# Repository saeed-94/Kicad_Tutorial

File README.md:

# Kicad Tutorial
* STM32F030 Circuit

*pcb Layout Top*

*pcb Layout Bottom*

## Shematic

## FreeCad
*pcb Layout Top*

*pcb Layout Top*

Hints:
* Circuit design in two layers with kicad version 5.1.5.

* 3D mode USB connector of the site: https://www.snapeda.com/parts/1050170001/Molex/view-part/?ref=search&t=USB_Micro-B_Molex-105017-0001

* In addition to wiring all routes, polygon is also considered ground and is located in the first layer.

* Circuit design with easyeda software: (Folder (doc)>-easyeda.pdf)

# Relay Module

*pcb Layout*

## Shematic

## FreeCad
*pcb 3d Layout*

For 3d Model we used kicadStepUpMod in FreeCAD software.

Hints:
* Circuit design in two layers with kicad version 5.1.9.

## Installing
Download and install your corresponding version of FreeCAD from https://wiki.freecadweb.org/Download

automatically using the FreeCAD Add-on Manager (https://github.com/FreeCAD/FreeCAD-addons) (bundled in to 0.17 dev version under Tools Menu)
manually by copying the kicadStepUpMod folder to the Mod sub-directory of the FreeCAD application.

## Designer
Saeed Ghorbani

Email: sa_ghorbani95@yahoo.com

Linkedin: www.linkedin.com/in/saeedghorbani

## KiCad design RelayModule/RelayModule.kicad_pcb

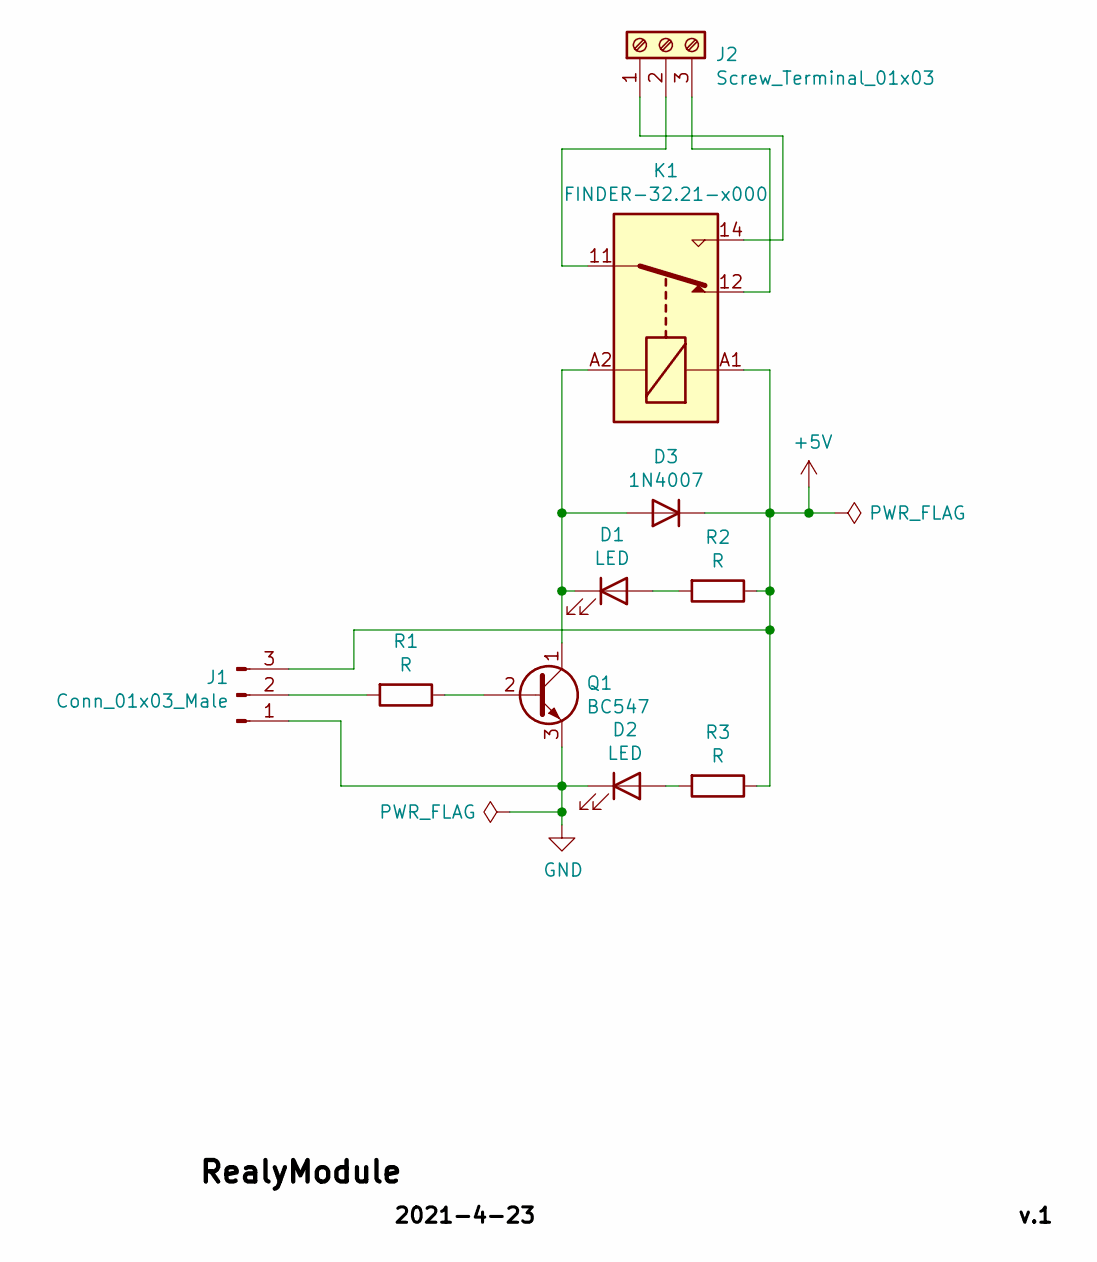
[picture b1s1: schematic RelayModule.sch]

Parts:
D1, D2: LED; LED_D3.0mm
D3: 1N4007; D_DO-41_SOD81_P10.16mm_Horizontal
J1: Conn_01x03_Male; PinHeader_1x03_P2.00mm_Vertical
J2: Screw_Terminal_01x03; TerminalBlock_Phoenix_MKDS-1,5-3_1x03_P5.00mm_Horizontal
K1: FINDER-32.21-x000; Relay_SPDT_Finder_36.11
Q1: BC547; TO-92
R1, R2, R3: R; R_Axial_DIN0411_L9.9mm_D3.6mm_P25.40mm_Horizontal

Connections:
+5V: D3.1 (K), J1.3, K1.A1, R2.1, R3.1
GND: D2.1 (K), J1.1, Q1.3 (E)
unnamed: D1.1 (K), D3.2 (A), K1.A2, Q1.1 (C)
unnamed: D1.2 (A), R2.2
unnamed: D2.2 (A), R3.2
unnamed: J1.2, R1.2
unnamed: J2.1, K1.14
unnamed: J2.2, K1.11
unnamed: J2.3, K1.12
unnamed: Q1.2 (B), R1.1

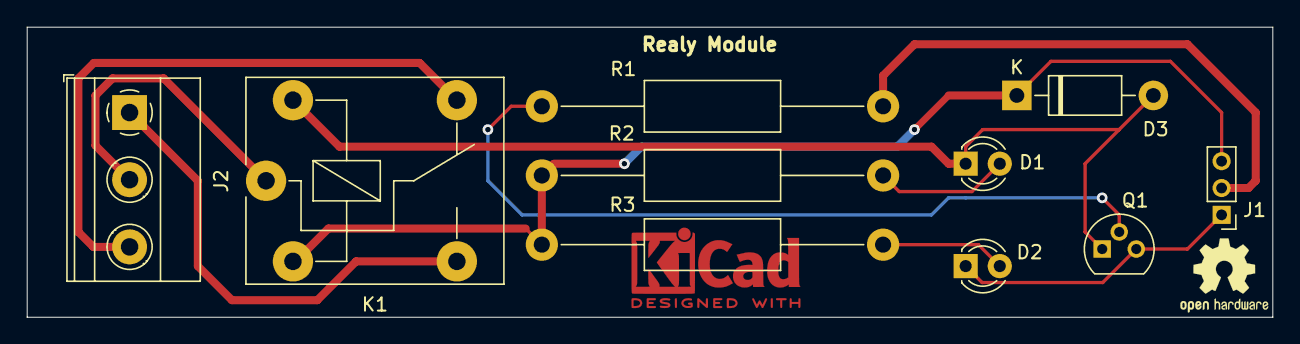
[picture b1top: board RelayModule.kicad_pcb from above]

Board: 2 copper layers, 92.7 x 21.6 mm, 10 parts (0 on the bottom side), 10 nets.

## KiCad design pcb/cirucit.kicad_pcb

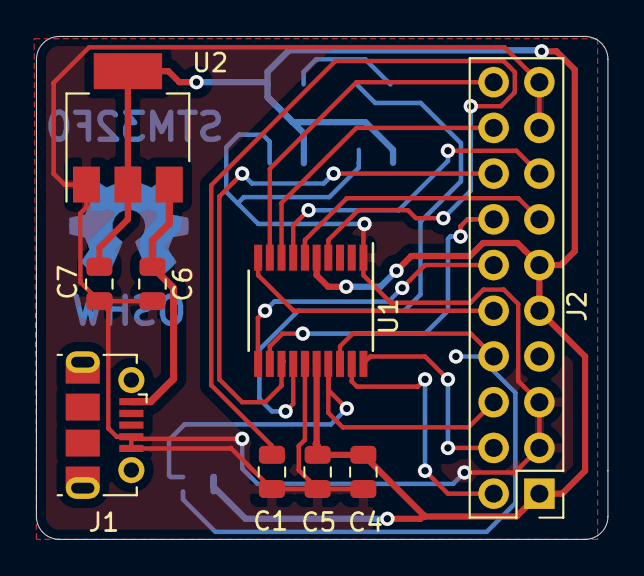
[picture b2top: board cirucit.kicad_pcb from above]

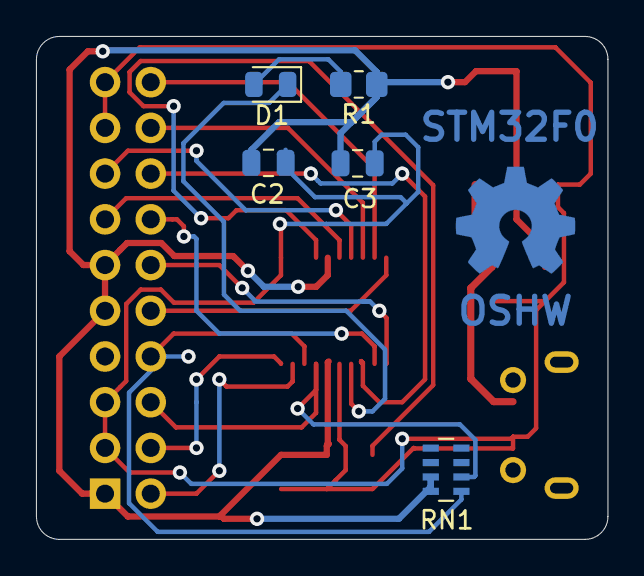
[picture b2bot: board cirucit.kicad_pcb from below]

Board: 2 copper layers, 31.8 x 27.9 mm, 14 parts (5 on the bottom side), 18 nets.

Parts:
C1: 0.1uF; C_0805_2012Metric
C2: 4.7uF; C_0805_2012Metric
C3: 100nF; C_0805_2012Metric
C4: 1uF; C_0805_2012Metric
C5: 10nF; C_0805_2012Metric
C6, C7: 10uF; C_0805_2012Metric
D1: LED; LED_0805_2012Metric
J1: USB_B; USB_Micro-B_Molex-105017-0001
J2: Conn_02x10_Odd_Even; PinHeader_2x10_P2.54mm_Vertical
R1: R; R_0805_2012Metric_Pad1.20x1.40mm_HandSolder
RN1: R_Pack04; R_Array_Concave_4x0603
U1: STM32F030F4Px; TSSOP-20_4.4x6.5mm_P0.65mm
U2: LD1117S33TR_SOT223; SOT-223-3_TabPin2

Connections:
+3V3: C2.1, C3.1, C4.1, C5.1, C7.1, J2.1, J2.9, J2.11, R1.1, RN1.3, RN1.4, U1.5, U1.16, U2.2
+5V: C6.1, J1.1, U2.3
ADC_IN0: J2.13, U1.6
ADC_IN1: J2.15, U1.7
GND: C1.2, C2.2, C3.2, C4.2, C5.2, C6.2, C7.2, J1.4, J1.5, J2.3, J2.5, J2.17, J2.19, U1.1, U1.15, U2.1
I2C1_SCL: J2.6, RN1.6, U1.17
I2C1_SDA: J2.8, RN1.5, U1.18
NRST: C1.1, U1.4
unnamed: D1.1, U1.14
unnamed: D1.2, R1.2
SPI1_MOSI: J2.16, U1.13
SPI1_NSS: J2.10, U1.10
SPI1_SCK: J2.12, U1.11
SPI_MISO: J2.14, U1.12
SWCLK: J2.4, U1.20
SWDIO: J2.2, U1.19
USART1_TX: J2.18, U1.8
USART_RX: J2.20, U1.9

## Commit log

2020-12-12 initial pcb
2021-02-08 STM32F0 design with easyeda software:
2021-02-08 "STM32F0 circuit with easyeda sotware"
2021-04-25 add Relay Module circuit
